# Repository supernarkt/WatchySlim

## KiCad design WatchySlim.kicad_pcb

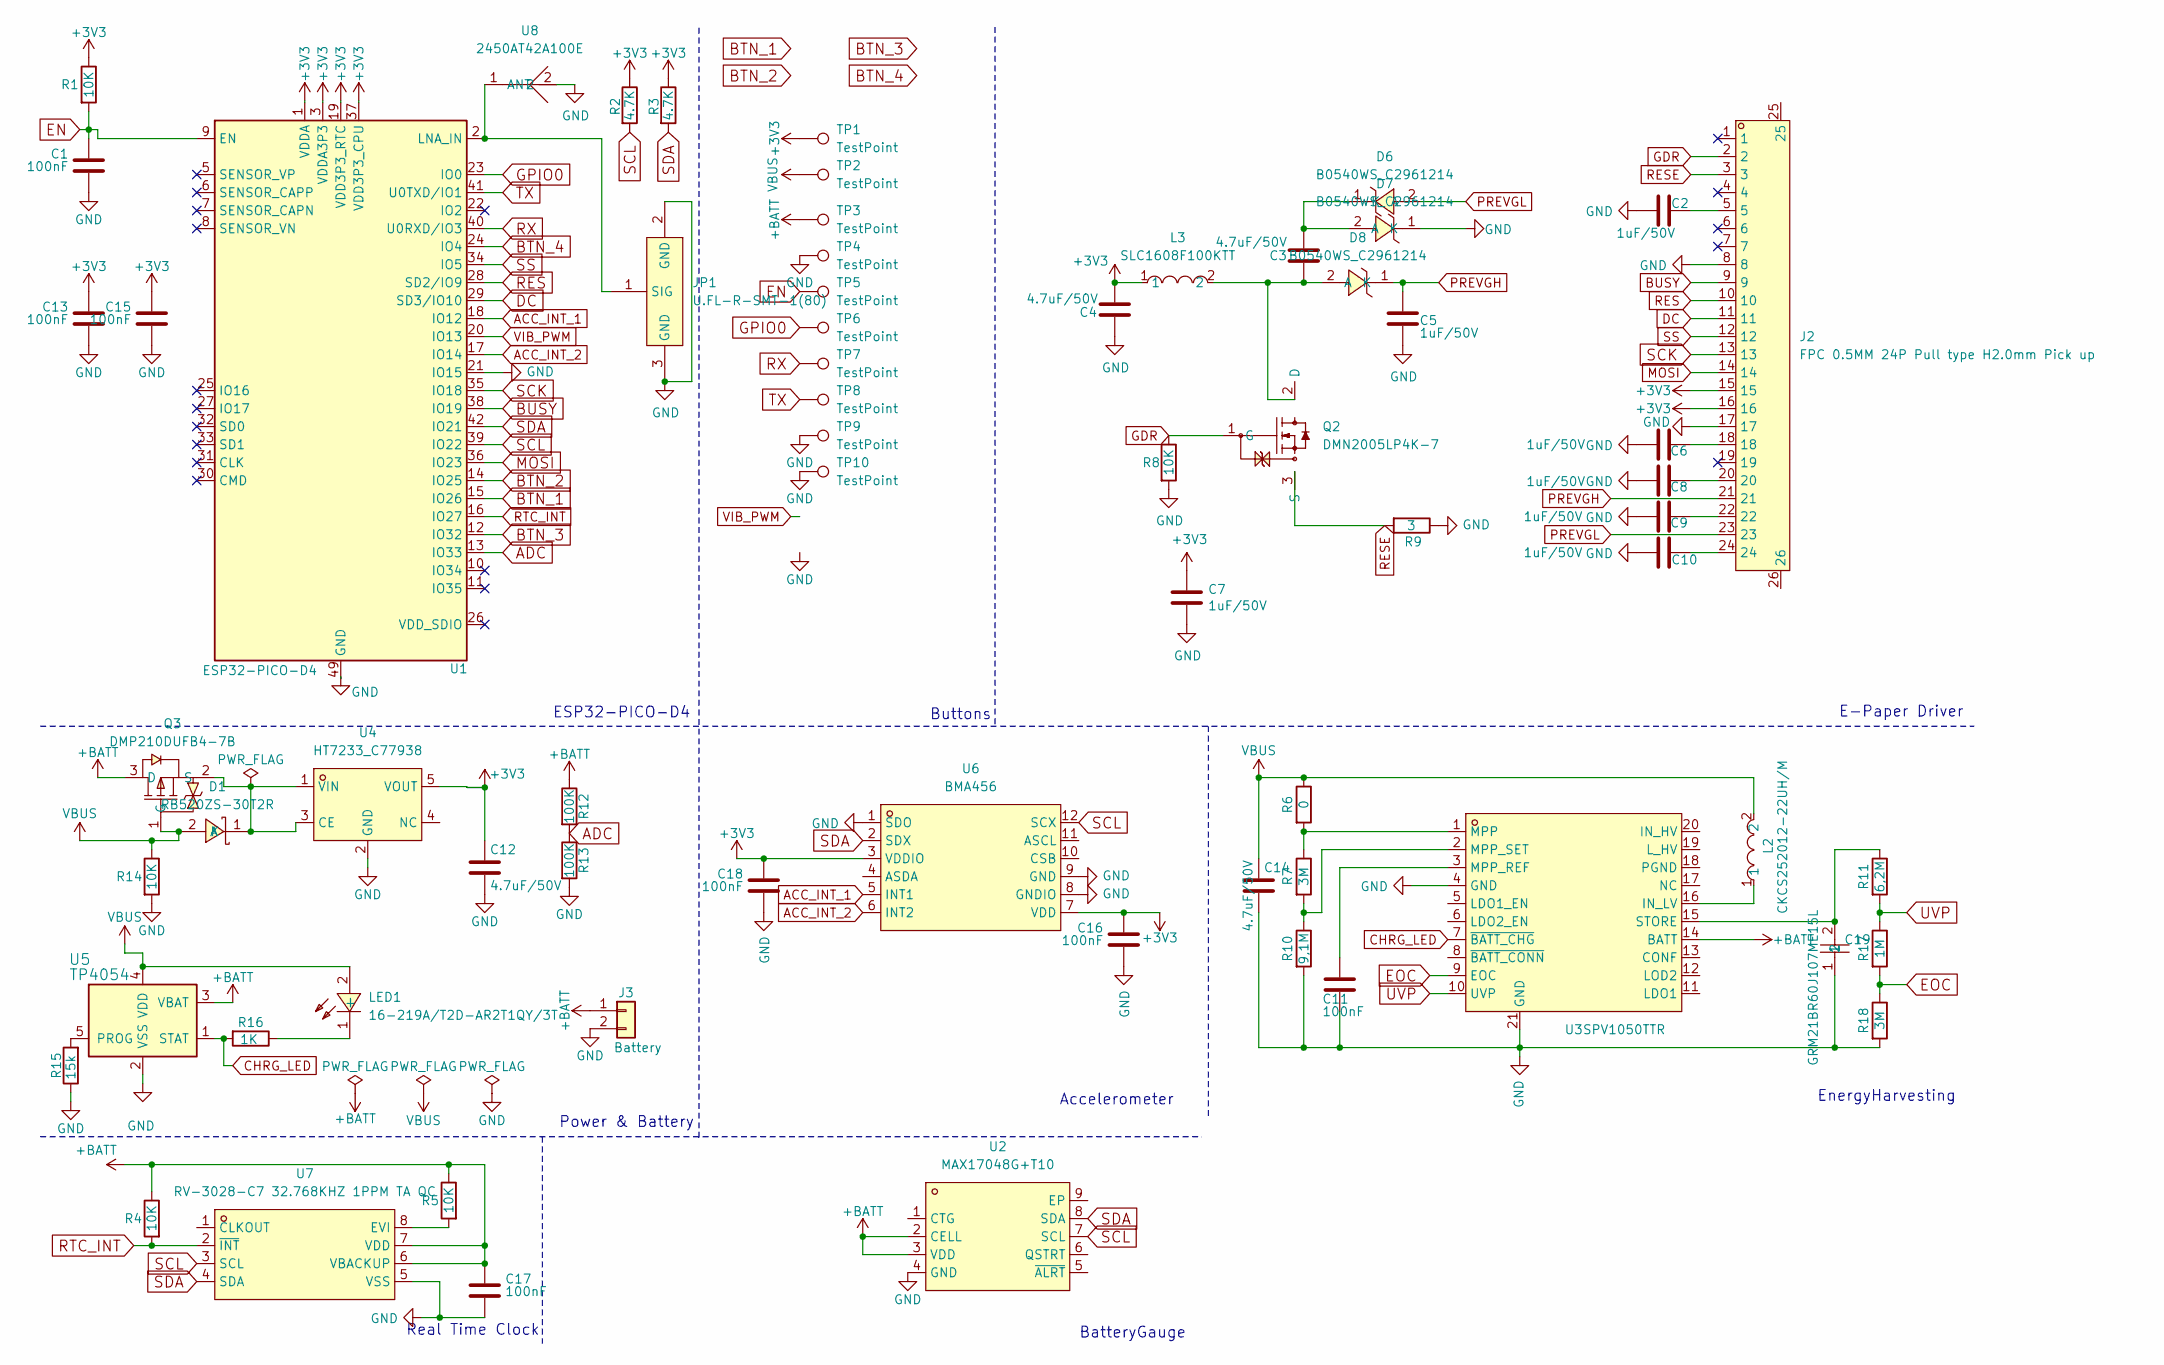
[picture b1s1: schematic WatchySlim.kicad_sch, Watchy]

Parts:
C1, C11, C13, C15, C16, C17, C18: 100nF; C_0402_1005Metric
C2, C5, C6, C7, C8, C9, C10: 1uF/50V; C_0402_1005Metric
C3, C12, C14: 4.7uF/50V; C_0402_1005Metric
C4: 4.7uF/50V; C_0805
C19: GRM21BR60J107ME15L; C0805; LCSC Part C141660
D1: RB520ZS-30T2R; SOD-962_L0.6-W0.3-RD; LCSC Part C129266
D6, D7, D8: B0540WS_C2961214; SOD-323_L1.7-W1.3-LS2.6-RD-1; LCSC Part C2961214
J2: FPC 0.5MM 24P Pull type H2.0mm Pick up; FPC-SMD_24P-L17.5-W5.4-P0.50; LCSC Part C11092
J3: Battery; L_Chilisin_BMRA00040420
JP1: U.FL-R-SMT-1(80); RF-SMD_FRF05002-JSS103M; LCSC Part C88374
L2: CKCS252012-22UH/M; IND-SMD_L2.5-W2.0; LCSC Part C354551
L3: SLC1608F100KTT; IND-SMD_L1.8-W1.2; LCSC Part C411908
LED1: 16-219A/T2D-AR2T1QY/3T; LED0402-R-RD; LCSC Part C74342
Q2: DMN2005LP4K-7; X2-DFN1006-3_L1.0-W0.6-P0.35-BL; LCSC Part C154746
Q3: DMP210DUFB4-7B; X2-DFN1006-3_L1.0-W0.6-BR; LCSC Part C443620
R1, R8, R14: 10K; R_0402
R2, R3: 4.7K; R_0402
R4, R5: 10K; C_0402_1005Metric
R6: 0; R_0402_1005Metric
R7, R18: 3M; R_0402_1005Metric
R9: 3; R_0402
R10: 9,1M; R_0402_1005Metric
R11: 6,2M; R_0402_1005Metric
R12: 100K; R_0402
R13: 100K; R_0402_1005Metric
R15: 15k; R_0402
R16: 1K; R_0402
R17: 1M; R_0402_1005Metric
TP1, TP2, TP3, TP4, TP5, TP6, TP7, TP8, TP9, TP10: TestPoint; TestPoint_THTPad_D1.0mm_Drill0.5mm
U1: ESP32-PICO-D4; QFN-48-1EP_7x7mm_Pitch0.5mm
U2: MAX17048G+T10; DFN-8_L2.0-W2.0-P0.50-BL-EP; LCSC Part C2682616
U3: SPV1050TTR; WQFN-20_L3.0-W3.0-P0.40-BL-EP1.7; LCSC Part C5181469
U4: HT7233_C77938; SOT-23-5_L3.0-W1.7-P0.95-LS2.8-BR; LCSC Part C77938
U5: TP4054; SOT-23-5
U6: BMA456; LGA-12_L2.0-W2.0-P0.50-BL; LCSC Part C189518
U7: RV-3028-C7 32.768KHZ 1PPM TA QC; OSC-SMD_8P-L3.2-W1.5-P0.90-BL; LCSC Part C3019759
U8: 2450AT42A100E; ANT-SMD_L5.0-W2.0; LCSC Part C2917719

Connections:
+3V3: C4.1, C7.1, C12.1, C13.1, C15.1, C16.1, C18.1, J2.15, J2.16, L3.1, R1.1, R2.1, R3.1, TP1.1, U1.1 (VDDA), U1.3 (VDDA3P3), U1.4 (VDDA3P3), U1.19 (VDD3P3_RTC), U1.37 (VDD3P3_CPU), U1.43 (VDDA), U1.46 (VDDA), U4.5 (VOUT), U6.3 (VDDIO), U6.7 (VDD)
+BATT: C17.1, J3.1, Q3.3 (D), R4.1, R5.1, R12.1, TP3.1, U2.2 (CELL), U2.3 (VDD), U3.14 (BATT), U5.3 (VBAT), U7.6 (VBACKUP), U7.7 (VDD)
ACC_INT_1: U1.18 (IO12), U6.5 (INT1)
ACC_INT_2: U1.17 (IO14), U6.6 (INT2)
ADC: R12.2, R13.1, U1.13 (IO33)
BTN_1: U1.15 (IO26)
BTN_2: U1.14 (IO25)
BTN_3: U1.12 (IO32)
BTN_4: U1.24 (IO4)
BUSY: J2.9, U1.38 (IO19)
CHRG_LED: R16.2, U3.7 (~BATT_CHG), U5.1 (STAT)
DC: J2.11, U1.29 (SD3/IO10)
EN: C1.1, R1.2, TP5.1, U1.9 (EN)
EOC: R17.2, R18.1, U3.9 (EOC)
GDR: J2.2, Q2.1 (G), R8.1
GND: C1.2, C2.2, C4.2, C5.2, C6.2, C7.2, C8.2, C9.2, C10.2, C11.2, C12.2, C13.2, C14.2, C15.2, C16.2, C17.2, C18.2, C19.1, D7.1 (K), J2.8, J2.17, J3.2, JP1.2 (GND), JP1.3 (GND), R8.2, R9.1, R10.2, R13.2, R14.2, R15.1, R18.2, TP4.1, TP9.1, TP10.1, U1.21 (IO15), U1.49 (GND), U2.4 (GND), U3.4 (GND), U3.21 (GND), U4.2 (GND), U5.2 (VSS), U6.1 (SDO), U6.8 (GNDIO), U6.9 (GND), U7.5 (VSS), U8.2
GPIO0: TP6.1, U1.23 (IO0)
MOSI: J2.14, U1.36 (IO23)
unnamed: C2.1, J2.5
unnamed: C6.1, J2.18
unnamed: C8.1, J2.20
unnamed: C9.1, J2.22
unnamed: C10.1, J2.24
unnamed: D1.1 (K), Q3.2 (S), U4.1 (VIN), U4.3 (CE)
unnamed: C3.1, D6.1 (K), D7.2 (A)
unnamed: C3.2, D8.2 (A), L3.2, Q2.2 (D)
unnamed: JP1.1 (SIG), U1.2 (LNA_IN), U8.1 (ANT)
unnamed: LED1.1 (-), R16.1
unnamed: L2.1, U3.16 (IN_LV)
unnamed: R6.2, R7.1, U3.1 (MPP)
unnamed: C11.1, U3.3 (MPP_REF)
unnamed: R7.2, R10.1, U3.2 (MPP_SET)
unnamed: C19.2, R11.1, U3.15 (STORE)
unnamed: R15.2, U5.5 (PROG)
unnamed: R5.2, U7.8 (EVI)
PREVGH: C5.1, D8.1 (K), J2.21
PREVGL: D6.2 (A), J2.23
RES: J2.10, U1.28 (SD2/IO9)
RESE: J2.3, Q2.3 (S), R9.2
RTC_INT: R4.2, U1.16 (IO27), U7.2 (~INT)
RX: TP7.1, U1.40 (U0RXD/IO3)
SCK: J2.13, U1.35 (IO18)
SCL: R2.2, U1.39 (IO22), U2.7 (SCL), U6.12 (SCX), U7.3 (SCL)
SDA: R3.2, U1.42 (IO21), U2.8 (SDA), U6.2 (SDX), U7.4 (SDA)
SS: J2.12, U1.34 (IO5)
TX: TP8.1, U1.41 (U0TXD/IO1)
UVP: R11.2, R17.1, U3.10 (UVP)
VBUS: C14.1, D1.2 (A), L2.2, LED1.2 (+), Q3.1 (G), R6.1, R14.1, TP2.1, U5.4 (VDD)
VIB_PWM: U1.20 (IO13)

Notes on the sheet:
E-Paper Driver
Real Time Clock
Accelerometer
BatteryGauge
Buttons
Power & Battery
ESP32-PICO-D4
EnergyHarvesting

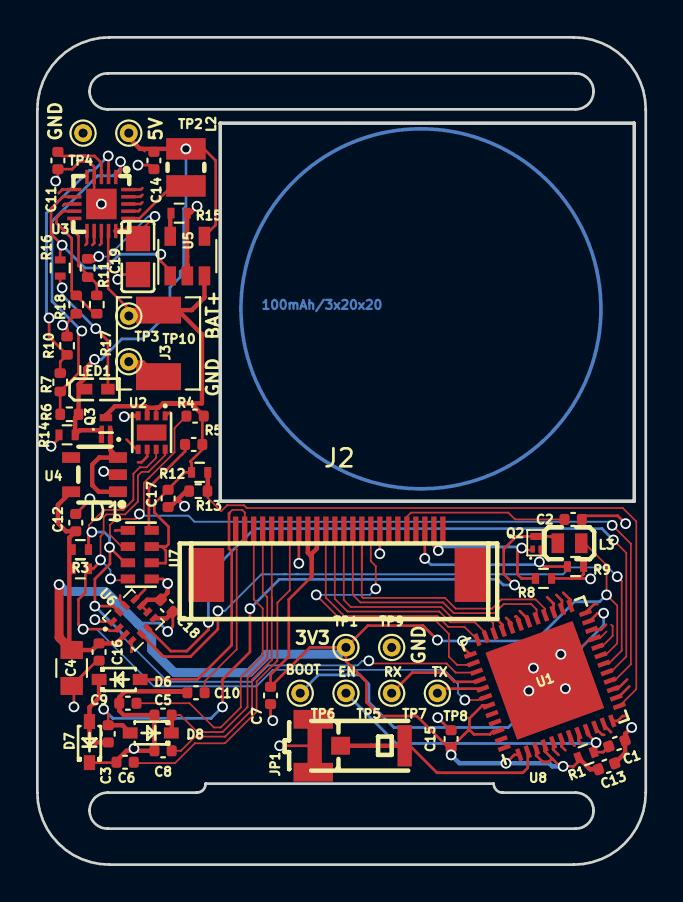
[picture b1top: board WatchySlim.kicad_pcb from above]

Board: 2 copper layers, 33.8 x 45.9 mm, 67 parts (0 on the bottom side), 44 nets.

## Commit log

2024-04-10 Init Commit WatchySlim
